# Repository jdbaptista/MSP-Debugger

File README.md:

## Introduction
This project is a combination of bare-metal firmware and hardware that displays the assembly instructions stored in the flash memory of an MSP430G2553, specifically the 20 pin DIP package. Please navigate to each section as necessary: [Example Operation](#example-operation), [Firmware](#firmware).

The device is shown below and supports the following button interactions:
* **UP**: Move back one instruction. Note that moving back one instruction is equivalent to moving lower in memory because the program counter increments positively each target CPU cycle.
  
* **DOWN**: Move forward one instruction. Note that moving forward one instruction is equivalent to moving higher in memory because the program counter increments positively each target CPU cycle.
  
* **FOLLOW JMP**: When the cursor is on a jump instruction, this button moves the cursor to the location specified by the jump. There is also support for following call instructions when the destination operand is an immediate or PC relative offset.
  
* **BIN <-> ASM**: Switch the display view between machine code (binary), displayed in hexadecimal, and RISC assembly instructions. This button highlights that assembly instructions on the target correspond to variable length machine code due to operand types.
  
* **RESET**: Move the cursor back to `0xC000`, which is the start of code memory. This is implemented by simply resetting the MCU.
  
* **USB RESET**: Reset the USB to UART bridge. USB data lines are currently in a broken state, so this button does nothing.

<br>

## Example Operation
The following example code from Texas Instruments is used in this example of the device's operation. The code blinks P1.0 repeatedly. Note that all assembly instructions displayed by the device are confirmed to be correct by Code Composer Studio's professional disassembler.
```C
#include <msp430.h>				

void main(void)
{
	WDTCTL = WDTPW | WDTHOLD;		// stop watchdog timer
	P1DIR |= 0x01;					// configure P1.0 as output

	volatile unsigned int i;		// volatile to prevent optimization

	while(1)
	{
		P1OUT ^= 0x01;				// toggle P1.0
		for(i=10000; i>0; i--);     // delay
	}
}
```
The target is loaded with the assembled machine code for this program and placed in the MSP-Debugger. Unfortunately, the display and USB to UART bridge are currently broken, so an MSP-FET (from any MSP430 development board) is connected to the JTAG header of the debugger. The MSP-FET's backchannel UART to USB bridge is used to convey instructions to the user, operating at **9600 baud with an 8-bit frame, no parity bit, and importantly 2 stop bits** (for data integrity). The UART encoding is ISO-8859-1, which is the default in CCS. Immediately after **RESET** the following instruction are extracted from the target and displayed.
```
0xC000: SUB.B #2 SP <
0xC002: MOV.B #0x5A80 &0x0120
0xC008: BIS.B #1 &0x0022
0xC00C: XOR.B #1 &0x0021
```
Using the **DOWN** button moves the cursor from `0xC000` to `0xC002`.
```
0xC002: MOV.B #0x5A80 &0x0120 <
0xC008: BIS.B #1 &0x0022
0xC00C: XOR.B #1 &0x0021
0xC010: MOV.B #0x2710 0x0000(SP)
```
An extremely well trained eye will recognize `&0x0120` as the location of the `WDTCTL` register, which can be confirmed by the peripheral file map on page 18 of the [MSP430G2x53 Datasheet](https://www.ti.com/lit/ds/symlink/msp430g2553.pdf?ts=1720602399535&ref_url=https%253A%252F%252Fwww.ti.com%252Fproduct%252FMSP430G2553%253Futm_source%253Dgoogle%2526utm_medium%253Dcpc%2526utm_campaign%253Depd-null-null-GPN_EN-cpc-pf-google-kr%2526utm_content%253DMSP430G2553%2526ds_k%253D%257B_dssearchterm%257D%2526DCM%253Dyes%2526gad_source%253D1%2526gclid%253DCjwKCAjw4ri0BhAvEiwA8oo6Fw8EdAuptheRVE8vx0Q2j3G3iyDjTU-aOLXieh8M-imSlC9cQUR6_hoClwEQAvD_BwE%2526gclsrc%253Daw.ds%2526bm-verify%253DAAQAAAAJ_____3QLXOZbbdruMI2eB4mFy5KSyEb-yU9yfcNR8-6ZE-F4IlQA15TnUbnZYGHUclM_YK0JJvwZfmZV1vz0BoNFahgPHVY7BCm4W1e8hj6dfjPbReoJt03aw_CYG9J3Y8_jl0rNTcSpbsnRtODv2ub_rMMIkYIZ8sZN9mj6PYFAQ1CDy5mA6PGPGiCbLLn4tzBTBUOk0bJGTj9kveVfehS7i0km-maJESLOX2xoAFatjT2Bv-a8B9gvZcxtGENvp6eMYJDLbmRf67x4X7TE7tt88LH3n9FraEEjZPNjqllkWuL5OOONuBvPF598xP5kkYnJk3wzH9hIroxr1CUU2mTA124pgKzPR_rSHUN9RBbZlIETbuTA60Tk97_1ntDEeGNxAcWS2jB9cD66YYZ0SP0K35RqUrqlAPRsbdokSfG5fS__GGfM8jKUantdnKKpmyNt6DdoRJ1r1NB9CKWKb-SPG5tTHcpbzj1IFa38Zdux2S1X93eAYTW28T1i1pfPwFwJtyAuMkVxw52pn_Y16Fv4n5pcFP_gVm7DHllf_3j6l4I_ipVjaMjKLlI1TF2-Ir8mL8IGx4NuPwbIxyWDxJgmZ_jNEwqQak_lFWplGfgBfkp1_twV8Zrt-tub-1XrNvhwLE4xQLYsvy4ZATQQBHijVjMIYRRXAuL75RCAAUYcWCXUhR5zKtjJhYKP3NkYnMghe8Nj_tdsmRdDuz-CPD87). Someone without access to the C source code can reference page 363 of the [MSP430G2xx User Guide](https://www.ti.com/lit/ug/slau144k/slau144k.pdf?ts=1720622345813&ref_url=https%253A%252F%252Fwww.ti.com%252Fproduct%252FMSP430F2274-EP%253Fbm-verify%253DAAQAAAAJ_____2GXDeU4IIaEds7sCQitbINeDMGTgqNh7F20H7LVJyrs5LsYNIkQrF5ycgp2Z0Yzd4j0V7synm_dgqfLwBr7S5VesPGUssLDDUfg7mGj_mgtHY82RE3zgMG80y9GDnAMYK8hv1U5Bq9QLLAvt0XehujFdDcILVLVdafgQQ4y_G74JWcE-jRRkwir5ItF99koK6Pg_AP0E-3rrXrP4YO819zT--lXgtbtaeA9YqF_kJtLNL18SaURyUQHTQi5XznOoq8sb0SznRHjyRujqGne18cY0YsrFImOVD6oPzmZqavXlbABc6vvCKw) to determine that the value `#0x5A80` being moved into `WDTCTL` register writes the correct watchdog password `0x5A00` (`WDTPW`) and suspends the watchdog's operation with `0x0080` (`WDTHOLD`). The watchdog timer will reset the microcontroller if not 'pet' in time by setting `WDTCNTCL`, so this instruction allows the microcontroller to operate without fear of the watchdog.

Using the **BIN <-> ASM** button switches the display from assembly to machine code.
```
0xC002: 0x40B2 0x5A80 0x0120 <
0xC008: 0xD3D2 0x0022 
0xC00C: 0xE3D2 0x0021 
0xC010: 0x40B1 0x2710 0x0000 
```
In this view it can be seen that the instruction to suspend the watchdog takes 3 words, ie. 48 bits, to encode. This is because the `MOV` instruction is a double operand instruction type and the opcode `0x40B2` specifies immediate mode for the first operand, which stores the immediate in the second word, and absolute mode for the second operand, which stores its address in the third word. These modes are internally specified by indirect autoincrement mode with the PC register and indexed mode with the SR register, respectively.

The while loop on line 1 should correspond to a jump instruction somewhere in memory, which we navigate forward to discover.
```
0xC01A: JEQ 0xC00C <
0xC01C: SUB.B #1 0x0000(SP)
0xC020: CMP.B #0 0x0000(SP)
0xC024: JEQ 0xC00C
```
The first jump instruction found is at `0xC01A`, jumping to `0xC00C`. This isn't useful in itself because we don't know what was being compared, which was an instruction that was skipped over.

Using the **UP** button moves the cursor backward by one instruction.
```
0xC016: CMP.B #0 0x0000(SP) <
0xC01A: JEQ 0xC00C
0xC01C: SUB.B #1 0x0000(SP)
0xC020: CMP.B #0 0x0000(SP)
```
This instruction is comparing 0 to some variable located at the stack pointer. This should be `i` from line 12 of the source code because it is the only variable on the stack. Therefore, the jump must correspond to finishing the delay.

Moving the cursor down to the `JEQ 0xC00C` isntruction and using the **FOLLOW JMP** instruction brings the cursor to `0xC00C`.
```
0xC00C: XOR.B #1 &0x0021 <
0xC010: MOV.B #0x2710 0x0000(SP)
0xC016: CMP.B #0 0x0000(SP)
0xC01A: JEQ 0xC00C
```
Finally, it is seen that this `XOR` instruction corresponds to toggling P1.0, as it is the first thing to occur within the while loop!

## Firmware
An MSP430G2553, aside from being the target type, is also used as the main microcontroller for the device. Firmware was developed using register level C programming in Code Composer Studio. Development followed information derived from the [MSP430G2xx User Guide](https://www.ti.com/lit/ug/slau144k/slau144k.pdf?ts=1720622345813&ref_url=https%253A%252F%252Fwww.ti.com%252Fproduct%252FMSP430F2274-EP%253Fbm-verify%253DAAQAAAAJ_____2GXDeU4IIaEds7sCQitbINeDMGTgqNh7F20H7LVJyrs5LsYNIkQrF5ycgp2Z0Yzd4j0V7synm_dgqfLwBr7S5VesPGUssLDDUfg7mGj_mgtHY82RE3zgMG80y9GDnAMYK8hv1U5Bq9QLLAvt0XehujFdDcILVLVdafgQQ4y_G74JWcE-jRRkwir5ItF99koK6Pg_AP0E-3rrXrP4YO819zT--lXgtbtaeA9YqF_kJtLNL18SaURyUQHTQi5XznOoq8sb0SznRHjyRujqGne18cY0YsrFImOVD6oPzmZqavXlbABc6vvCKw), the [MSP430G2x53 Datasheet](https://www.ti.com/lit/ds/symlink/msp430g2553.pdf?ts=1720602399535&ref_url=https%253A%252F%252Fwww.ti.com%252Fproduct%252FMSP430G2553%253Futm_source%253Dgoogle%2526utm_medium%253Dcpc%2526utm_campaign%253Depd-null-null-GPN_EN-cpc-pf-google-kr%2526utm_content%253DMSP430G2553%2526ds_k%253D%257B_dssearchterm%257D%2526DCM%253Dyes%2526gad_source%253D1%2526gclid%253DCjwKCAjw4ri0BhAvEiwA8oo6Fw8EdAuptheRVE8vx0Q2j3G3iyDjTU-aOLXieh8M-imSlC9cQUR6_hoClwEQAvD_BwE%2526gclsrc%253Daw.ds%2526bm-verify%253DAAQAAAAJ_____3QLXOZbbdruMI2eB4mFy5KSyEb-yU9yfcNR8-6ZE-F4IlQA15TnUbnZYGHUclM_YK0JJvwZfmZV1vz0BoNFahgPHVY7BCm4W1e8hj6dfjPbReoJt03aw_CYG9J3Y8_jl0rNTcSpbsnRtODv2ub_rMMIkYIZ8sZN9mj6PYFAQ1CDy5mA6PGPGiCbLLn4tzBTBUOk0bJGTj9kveVfehS7i0km-maJESLOX2xoAFatjT2Bv-a8B9gvZcxtGENvp6eMYJDLbmRf67x4X7TE7tt88LH3n9FraEEjZPNjqllkWuL5OOONuBvPF598xP5kkYnJk3wzH9hIroxr1CUU2mTA124pgKzPR_rSHUN9RBbZlIETbuTA60Tk97_1ntDEeGNxAcWS2jB9cD66YYZ0SP0K35RqUrqlAPRsbdokSfG5fS__GGfM8jKUantdnKKpmyNt6DdoRJ1r1NB9CKWKb-SPG5tTHcpbzj1IFa38Zdux2S1X93eAYTW28T1i1pfPwFwJtyAuMkVxw52pn_Y16Fv4n5pcFP_gVm7DHllf_3j6l4I_ipVjaMjKLlI1TF2-Ir8mL8IGx4NuPwbIxyWDxJgmZ_jNEwqQak_lFWplGfgBfkp1_twV8Zrt-tub-1XrNvhwLE4xQLYsvy4ZATQQBHijVjMIYRRXAuL75RCAAUYcWCXUhR5zKtjJhYKP3NkYnMghe8Nj_tdsmRdDuz-CPD87), and the [MSP430 JTAG Programming Guide](https://www.ti.com/lit/ug/slau320aj/slau320aj.pdf?ts=1720599451382&ref_url=https%253A%252F%252Fwww.google.com%252F). Three libraries were developed to handle separate facets of the project requirements:

* **UART Driver**: This library handles control of the USCI peripheral to communicate via the UART module. This driver handles configuration of USCI and UART registers, buffering of user printing output, and transmission with a builtin interrupt handler. The driver offers a user-friendly API (ex. `wait_print(char *input)` and `uart_print_hex(uint16_t input)`) optimized for spaced calls. The `wait_print` function is most likely to be used, and currently implements polling until the previous message is finished being sent.
  
* **JTAG Driver**: This library handles interfacing with the target through its JTAG debugging interface. Internally, the interface is implemented as an FSM that is controlled by five input and output lines: TDI, TDO, TMS, TCK, and TEST. This driver works by bit banging the correct FSM sequences on GPIO pins. The API offers a variety of functions (specified by the [JTAG Programming Guide](https://www.ti.com/lit/ug/slau320aj/slau320aj.pdf?ts=1720599451382&ref_url=https%253A%252F%252Fwww.google.com%252F)), but the most important for this project is `readMem(uint16_t address)`. This function returns the value stored in the target at a particular memory address.
  
* **Disassembler**: This library handles conversion of machine code to RISC assembly instruction. Information about the representation of each instruction as machine code can be found in the [MSP430G2xx User Guide](https://www.ti.com/lit/ug/slau144k/slau144k.pdf?ts=1720622345813&ref_url=https%253A%252F%252Fwww.ti.com%252Fproduct%252FMSP430F2274-EP%253Fbm-verify%253DAAQAAAAJ_____2GXDeU4IIaEds7sCQitbINeDMGTgqNh7F20H7LVJyrs5LsYNIkQrF5ycgp2Z0Yzd4j0V7synm_dgqfLwBr7S5VesPGUssLDDUfg7mGj_mgtHY82RE3zgMG80y9GDnAMYK8hv1U5Bq9QLLAvt0XehujFdDcILVLVdafgQQ4y_G74JWcE-jRRkwir5ItF99koK6Pg_AP0E-3rrXrP4YO819zT--lXgtbtaeA9YqF_kJtLNL18SaURyUQHTQi5XznOoq8sb0SznRHjyRujqGne18cY0YsrFImOVD6oPzmZqavXlbABc6vvCKw), specifically the CPU section. The MSP430G2553 contains a 16-bit CPU supporting variable length instructions ranging from a minimum of 1 word to a maximum of 3 words. This presented a significant design challenge as moving one assembly instruction backward is ambiguously a shift of 1, 2, or 3 words in memory with little to hint at which is correct. This ambiguity stems from the various addressing modes (ex. indexed mode) and instruction types (ex. single operand). The disassembler has no remedy to this issue; rather, it is currently solved by the main program which simply begins from the beginning of flash memory and iterates forward until finding the correct instruction. It is planned to speed up this process with a significantly sized cache of nearby instruction locations.

The main program handles user button input with interrupts on the corresponding GPIO pins and a simple button debounce system using the timer peripheral. The program enters LPM3 while waiting for user input, with the timer running on ACLK sourced from the 12kHz VLO waking the program up if a button debounce has finished.

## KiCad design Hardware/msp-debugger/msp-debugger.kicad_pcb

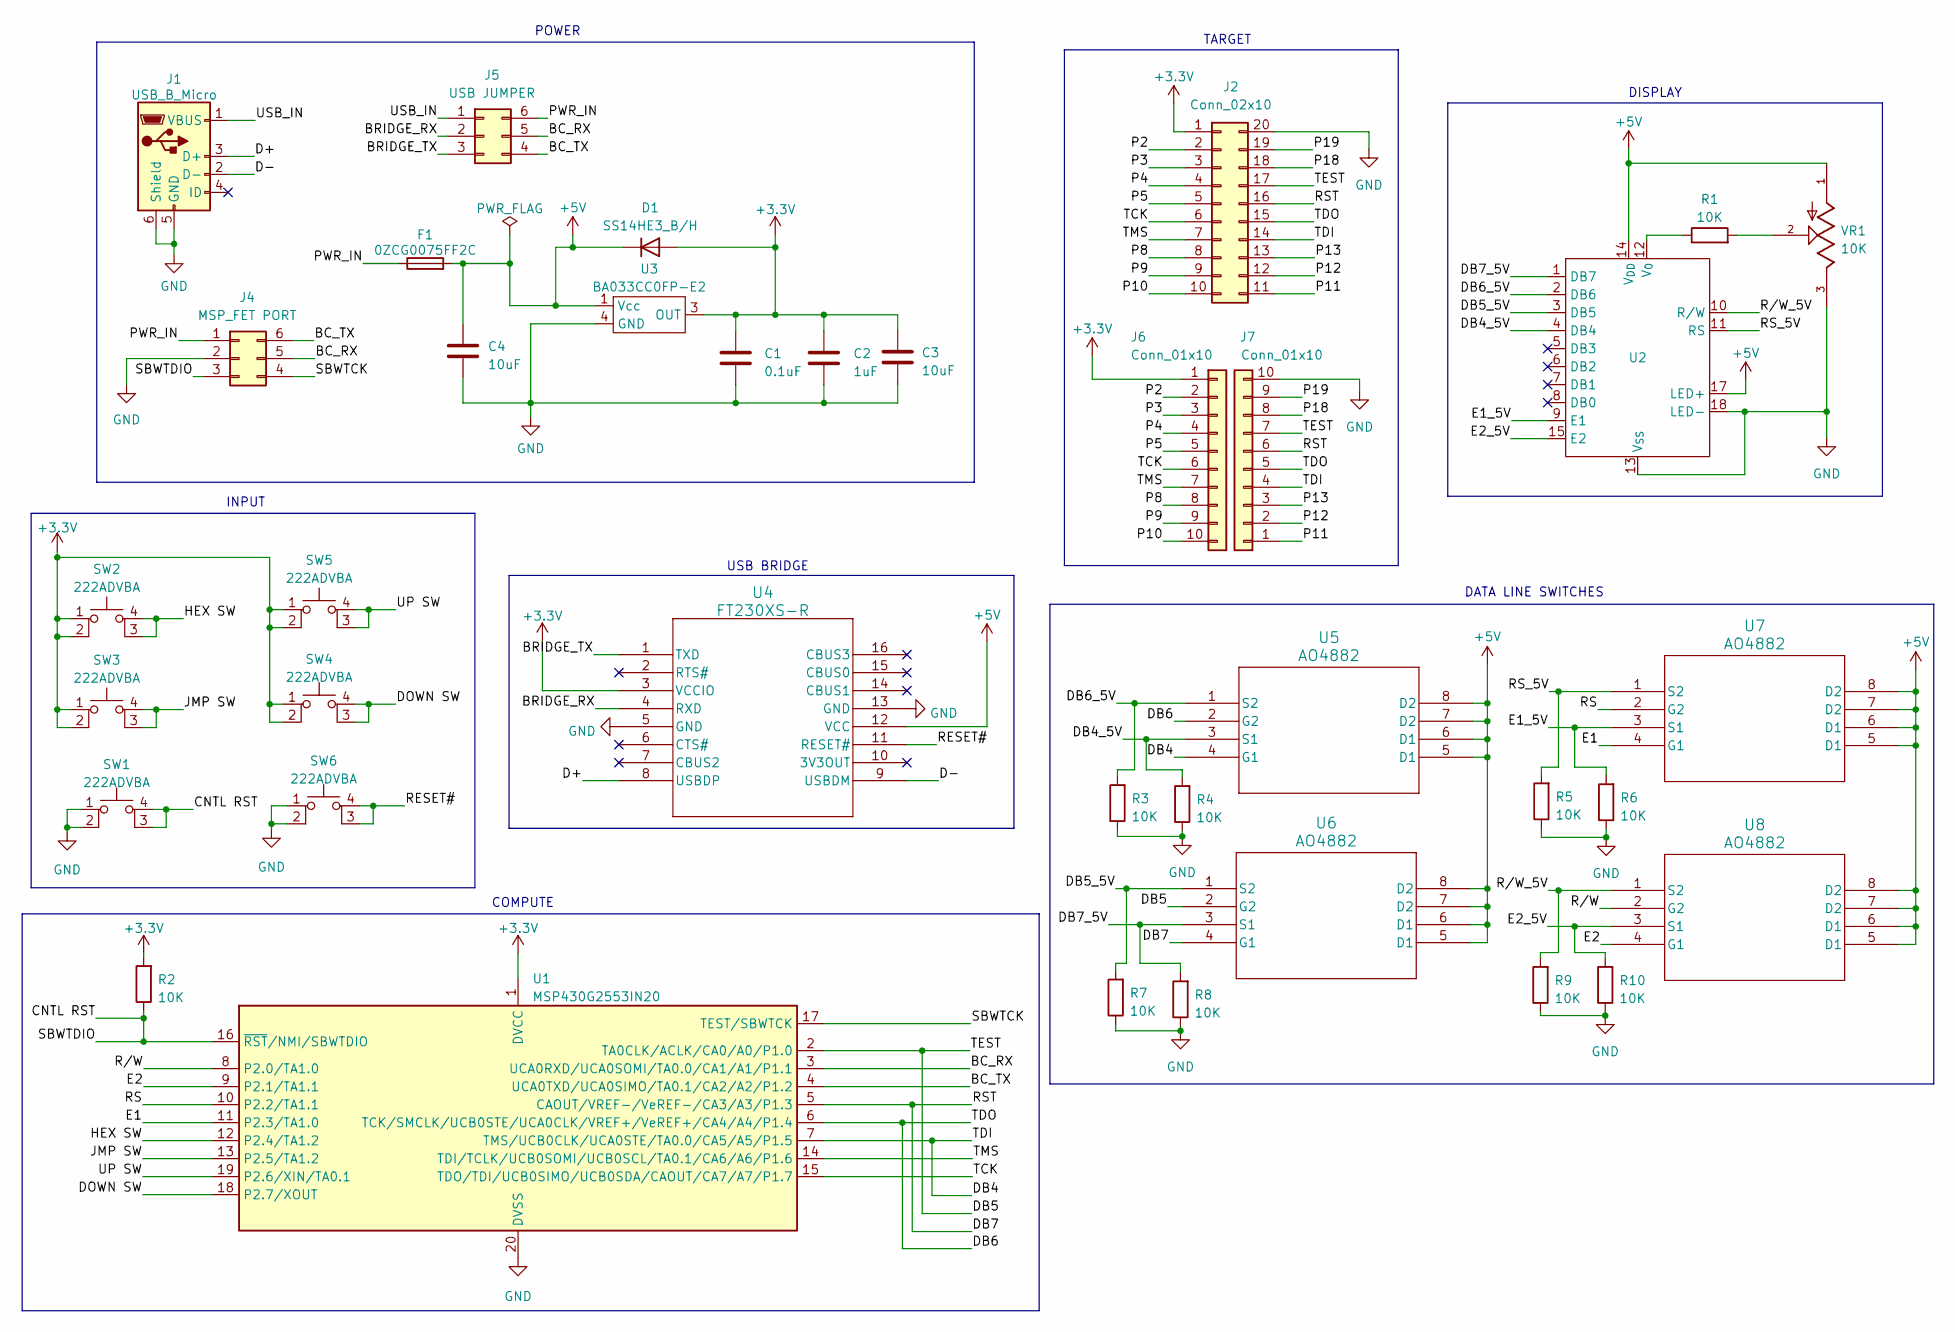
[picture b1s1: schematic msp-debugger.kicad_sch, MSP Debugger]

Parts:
C1: 0.1uF; C_0805_2012Metric
C2: 1uF; C_0805_2012Metric
C3, C4: 10uF; C_0805_2012Metric
D1: SS14HE3_B/H; D_SMA
F1: 0ZCG0075FF2C; Fuse_1812_4532Metric
J1: USB_B_Micro; PinHeader_1x05_P2.54mm_Vertical
J2: Conn_02x10; DIL_CONN_110-83-320-41-001101
J4: MSP_FET PORT; PinHeader_2x03_P2.54mm_Vertical
J5: USB JUMPER; PinHeader_2x03_P2.54mm_Vertical
J6, J7: Conn_01x10; PinHeader_1x10_P2.54mm_Vertical
R1, R2, R3, R4, R5, R6, R7, R8, R9, R10: 10K; C_0805_2012Metric
SW1, SW2, SW3, SW4, SW5, SW6: 222ADVBA; SW_222ADVBA
U1: MSP430G2553IN20; DIP-20_W7.62mm
U2: PinHeader_2x09_P2.54mm_Vertical
U3: BA033CC0FP-E2; TO-252-3
U4: FT230XS-R; SOIC_30XS-R_FTD
U5, U6, U7, U8: AO4882; SO-8_AOS
VR1: 10K; TRIM_3362P-1-103LF; PARTREV 08/26/10

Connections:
+3.3V: C1.2, C2.1, C3.1, D1.2 (A), J2.1, J6.1, R2.2, SW2.1, SW2.2, SW3.1, SW3.2, SW4.1, SW4.2, SW5.1, SW5.2, U1.1 (DVCC), U3.3 (OUT), U4.3 (VCCIO)
+5V: C4.1, D1.1 (K), F1.2, U2.14 (V_{DD}), U2.17 (LED+), U3.1 (Vcc), U4.12 (VCC), U5.5 (D1), U5.6 (D1), U5.7 (D2), U5.8 (D2), U6.5 (D1), U6.6 (D1), U6.7 (D2), U6.8 (D2), U7.5 (D1), U7.6 (D1), U7.7 (D2), U7.8 (D2), U8.5 (D1), U8.6 (D1), U8.7 (D2), U8.8 (D2), VR1.1
/BC_RX: J4.5, J5.5, U1.3 (UCA0RXD/UCA0SOMI/TA0.0/CA1/A1/P1.1)
/BC_TX: J4.6, J5.4, U1.4 (UCA0TXD/UCA0SIMO/TA0.1/CA2/A2/P1.2)
/BRIDGE_RX: J5.2, U4.4 (RXD)
/BRIDGE_TX: J5.3, U4.1 (TXD)
/CNTL RST: J4.3, R2.1, SW1.3 (K), SW1.4 (A), U1.16 (~RST/NMI/SBWTDIO)
/D+: J1.3 (D+), U4.8 (USBDP)
/D-: J1.2 (D-), U4.9 (USBDM)
/DB4: J2.14, J7.4, U1.7 (TMS/UCB0CLK/UCA0STE/TA0.0/CA5/A5/P1.5), U5.4 (G1)
/DB4_5V: R4.2, U2.4 (DB4), U5.3 (S1)
/DB5: J2.17, J7.7, U1.2 (TA0CLK/ACLK/CA0/A0/P1.0), U6.2 (G2)
/DB5_5V: R7.2, U2.3 (DB5), U6.1 (S2)
/DB6: J2.15, J7.5, U1.6 (TCK/SMCLK/UCB0STE/UCA0CLK/VREF+/VeREF+/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), U5.2 (G2)
/DB6_5V: R3.2, U2.2 (DB6), U5.1 (S2)
/DB7: J2.16, J7.6, U1.5 (CAOUT/VREF-/VeREF-/CA3/A3/P1.3), U6.4 (G1)
/DB7_5V: R8.2, U2.1 (DB7), U6.3 (S1)
/DOWN SW: SW4.3 (K), SW4.4 (A), U1.18 (P2.7/XOUT)
/E1: U1.11 (P2.3/TA1.0), U7.4 (G1)
/E1_5V: R6.2, U2.9 (E1), U7.3 (S1)
/E2: U1.9 (P2.1/TA1.1), U8.4 (G1)
/E2_5V: R10.2, U2.15 (E2), U8.3 (S1)
/HEX SW: SW2.3 (K), SW2.4 (A), U1.12 (P2.4/TA1.2)
/JMP SW: SW3.3 (K), SW3.4 (A), U1.13 (P2.5/TA1.2)
/P2: J2.2, J6.2
/P3: J2.3, J6.3
/P4: J2.4, J6.4
/P5: J2.5, J6.5
/P8: J2.8, J6.8
/P9: J2.9, J6.9
/P10: J2.10, J6.10
/P11: J2.11, J7.1
/P12: J2.12, J7.2
/P13: J2.13, J7.3
/P18: J2.18, J7.8
/P19: J2.19, J7.9
/PWR_IN: F1.1, J4.1, J5.6
/RESET#: SW6.3 (K), SW6.4 (A), U4.11 (RESET#)
/RS: U1.10 (P2.2/TA1.1), U7.2 (G2)
/RS_5V: R5.2, U2.11 (RS), U7.1 (S2)
/R/W: U1.8 (P2.0/TA1.0), U8.2 (G2)
/R/W_5V: R9.2, U2.10 (R/W), U8.1 (S2)
/SBWTCK: J4.4, U1.17 (TEST/SBWTCK)
/TCK: J2.6, J6.6, U1.15 (TDO/TDI/UCB0SIMO/UCB0SDA/CAOUT/CA7/A7/P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)
/TMS: J2.7, J6.7, U1.14 (TDI/TCLK/UCB0SOMI/UCB0SCL/TA0.1/CA6/A6/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)
/UP SW: SW5.3 (K), SW5.4 (A), U1.19 (P2.6/XIN/TA0.1)
/USB_IN: J1.1 (VBUS), J5.1
GND: C1.1, C2.2, C3.2, C4.2, J1.5 (GND), J1.6 (Shield), J2.20, J4.2, J7.10, R3.1, R4.1, R5.1, R6.1, R7.1, R8.1, R9.1, R10.1, SW1.1, SW1.2, SW6.1, SW6.2, U1.20 (DVSS), U2.13 (V_{SS}), U2.18 (LED-), U3.4 (GND), U4.5 (GND), U4.13 (GND), VR1.3
unnamed: R1.2, VR1.2
unnamed: R1.1, U2.12 (V_{0})

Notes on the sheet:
POWER
DATA LINE SWITCHES
USB BRIDGE
INPUT
COMPUTE
TARGET
DISPLAY

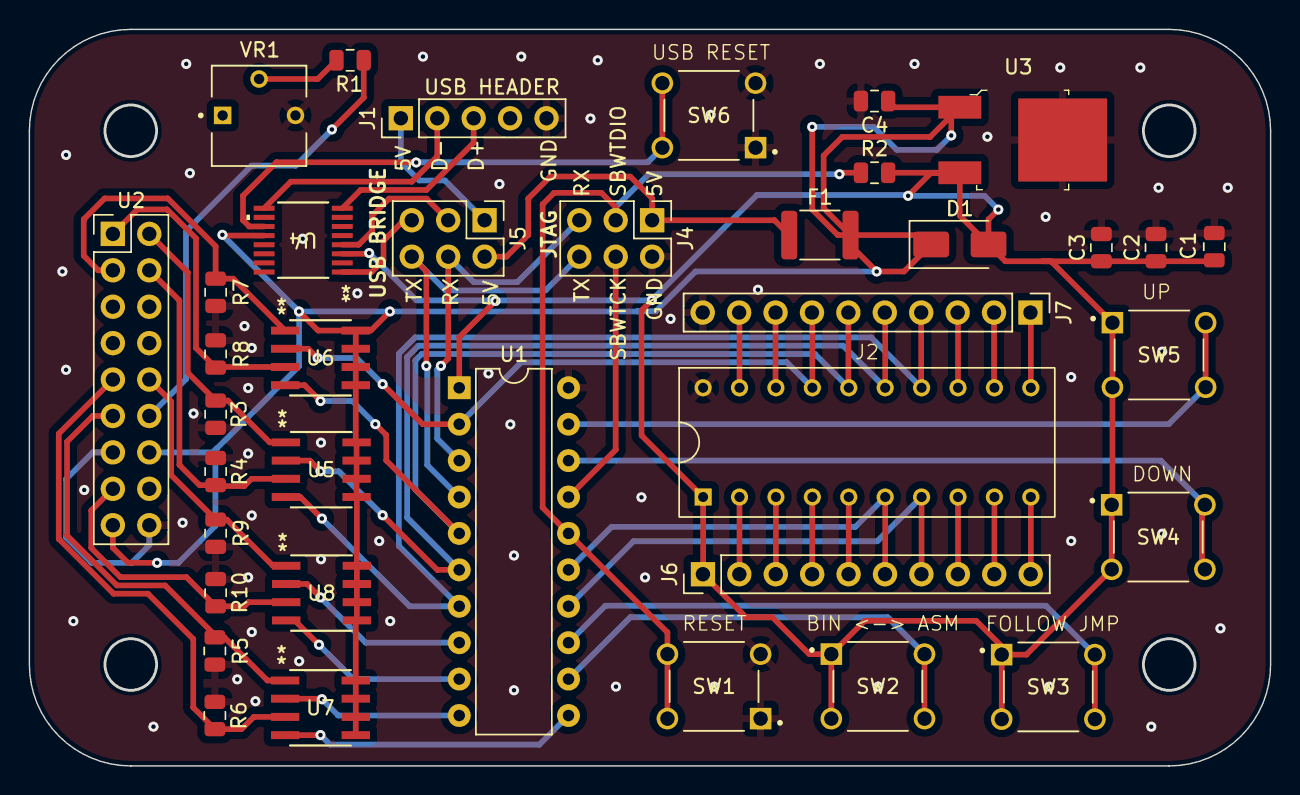
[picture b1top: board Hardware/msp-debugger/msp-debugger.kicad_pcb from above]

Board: 2 copper layers, 86.5 x 51.3 mm, 37 parts (0 on the bottom side), 50 nets.

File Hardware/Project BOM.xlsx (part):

Partner 1 Name: Jaden Baptista | Partner 1 Email: baptistajaden@berkeley.edu | Partner 2 Name: Anthony Rubio | Partner 2 Email: anthonyjrubio@berkeley.edu
 |  |  |  |  |  |  |  |  |  | Total Price for Project
 |  |  |  |  |  |  |  |  |  | 59.543329999999997
Qty (for 1 board) | Manufacturer Part # | Digi-key Part#/SKU | Price/unit ($) | Purchase URL | Reference Designator | Description (include component value if applicable) | Datasheet Link | Multiple | Total Qty | Total Price/part ($)
1 | NHD-0440AZ-FL-YBW | NHD-0440AZ-FL-YBW-ND | 28.59 | https://www.digikey.com/en/products/detail/newhaven-display-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 | U2 | LCD MOD 160 DIG 40X4 TRANS YLW/GRN | https://newhavendisplay.com/content/specs/NHD-0440AZ-FL-YBW.pdf | 1 | 1 | 28.59
10 | RC0805JR-0710KL | 311-10KARCT-ND | 0.1 | https://www.digikey.com/en/products/detail/yageo/RC0805JR-07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 | R1 | RES 10K OHM 5% 1/8W 0805 | https://www.yageo.com/upload/media/product/productsearch/dat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 | 1 | 10 | 1
1 | 3362P-1-103LF | 3362P-103LF-ND | 1.03 | https://www.digikey.com/en/products/detail/bourns-inc/3362P-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 | VR1 | TRIMMER 10K OHM 0.5W PC PIN TOP | https://www.bourns.com/docs/Product-Datasheets/3362.pdf | 1 | 1 | 1.03
6 | 222ADVBA | CT3084-ND | 0.23 | https://www.digikey.com/en/products/detail/cts-electrocompon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 | SW(1-5) | SWITCH TACTILE SPST-NO 0.05A 12V | https://www.ctscorp.com/wp-content/uploads/222A.pdf | 1 | 6 | 1.3800000000000001
3 | CL21B104KBCNNNC | 1276-1003-1-ND | 0.1 | https://www.digikey.com/en/products/detail/samsung-electro-m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 | C2, C5, C6 | CAP CER 0.1UF 50V X7R 0805 | https://media.digikey.com/pdf/Data%20Sheets/Samsung%20PDFs/C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 | 1 | 3 | 0.30000000000000004
2 | MSP430G2553IN20 | 296-28429-5-ND | 2.9 | https://www.digikey.com/en/products/detail/texas-instruments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 | U1, J1 | IC MCU 16BIT 16KB FLASH 20DIP | https://www.ti.com/general/docs/suppproductinfo.tsp?distId=1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 | 1 | 2 | 5.8
1 | 110-83-320-41-001101 | 110-83-320-41-001101-ND | 2.02 | https://www.digikey.com/en/products/detail/preci-dip/110-83-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 | J2 | CONN IC DIP SOCKET 20POS GOLD | https://www.mouser.com/datasheet/2/571/Preci_Dip_01252017_ca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 | 1 | 1 | 2.02
1 | CL21B105KAFNNNE | 1276-1066-1-ND | 0.1 | https://www.digikey.com/en/products/detail/samsung-electro-m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 | C1 | 1 µF ±10% 25V Ceramic Capacitor X7R 0805 (2012 Metric) | https://media.digikey.com/pdf/Data%20Sheets/Samsung%20PDFs/C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 | 1 | 1 | 0.1
1 | BA033CC0FP-E2 | BA033CC0FP-E2CT-ND | 1.41 | https://www.digikey.com/en/products/detail/rohm-semiconducto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 | U3 | IC REG LINEAR 3.3V 1A TO252-3 | https://www.rohm.com/datasheet?p=BA033CC0FP&dist=Digi-key&me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 | 1 | 1 | 1.41
1 | SS14HE3_B/H | 112-SS14HE3_B/HCT-ND | 9.7519999999999996E-2 | https://www.digikey.com/en/products/detail/vishay-general-se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 | D1 | Diode 40 V 1A Surface Mount DO-214AC (SMA) | https://www.vishay.com/docs/88746/ss12.pdf | 1 | 1 | 9.7519999999999996E-2
1 | 10118194-0011LF | 10118194-0011LF-ND | 0.27581 | https://www.digikey.com/en/products/detail/amphenol-icc-fci/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 | J1 | USB - micro B USB 2.0 Receptacle Connector 5 Position Surface Mount, Right Angl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 | https://cdn.amphenol-cs.com/media/wysiwyg/files/drawing/1011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 | 1 | 1 | 0.27581
1 | 0ZCG0075FF2C | 507-1763-1-ND | 0.16 | https://www.digikey.com/en/products/detail/bel-fuse-inc/0ZCG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 | F1 | PTC RESET FUSE 16V 750MA 1812 | https://www.belfuse.com/resources/datasheets/circuitprotecti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 | 1 | 1 | 0.16
2 | CL21A106KOQNNNE | 1276-1096-1-ND | 0.1 | https://www.digikey.com/en/products/detail/samsung-electro-m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 | C3, C4 | 10 µF ±10% 16V Ceramic Capacitor X5R 0805 (2012 Metric) | https://media.digikey.com/pdf/Data%20Sheets/Samsung%20PDFs/C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 | 1 | 2 | 0.2
1 | FT230XS-R | 768-1135-1-ND | 2.2599999999999998 | https://www.digikey.com/en/products/detail/ftdi-future-techn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 | U4 | IC USB SERIAL BASIC UART 16SSOP | https://ftdichip.com/wp-content/uploads/2021/10/DS_FT230X.pdf | 1 | 1 | 2.2599999999999998
4 | AO4882 | 785-1317-1-ND | 0.52 | https://www.digikey.com/en/products/detail/alpha-omega-semic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 |  | Mosfet Array 40V 8A 2W Surface Mount 8-SOIC | https://www.digikey.com/htmldatasheets/production/1034359/0/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 | 1 | 4 | 2.08
2 | TSW-102-07-G-T | TSW-102-07-G-T-ND | 0.73 | https://www.digikey.com/en/products/detail/samtec-inc/TSW-10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 | J4, J5 | CONN HEADER VERT 6POS 2.54MM | https://mm.digikey.com/Volume0/opasdata/d220001/medias/docus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 | 1 | 2 | 1.46
3 | QPC02SXGN-RC | S9337-ND | 0.1 | https://www.digikey.com/en/products/detail/sullins-connector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 |  | CONN JUMPER SHORTING .100" GOLD | https://s3.amazonaws.com/catalogspreads-pdf/PAGE128-129%20.1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 | 1 | 3 | 0.30000000000000004
2 | TD-109-T-A | SAM1114-09-ND | 3.6 | https://www.digikey.com/en/products/detail/samtec-inc/TD-109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 |  | CONN HEADER VERT 18POS 2.54MM | https://suddendocs.samtec.com/catalog_english/td.pdf | 1 | 2 | 7.2
2 | TS-110-T-A | SAM1112-10-ND | 1.94 | https://www.digikey.com/en/products/detail/samtec-inc/TS-110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 |  | CONN HEADER VERT 10POS 2.54MM | https://suddendocs.samtec.com/catalog_english/td.pdf | 1 | 2 | 3.88
 |  |  |  |  |  |  |  |  | 0 | 0
 |  |  |  |  |  |  |  |  | 0 | 0
 |  |  |  |  |  |  |  |  | 0 | 0
 |  |  |  |  |  |  |  |  | 0 | 0
 |  |  |  |  |  |  |  |  | 0 | 0
 |  |  |  |  |  |  |  |  | 0 | 0
 |  |  |  |  |  |  |  |  | 0 | 0
 |  |  |  |  |  |  |  |  | 0 | 0
 |  |  |  |  |  |  |  |  | 0 | 0
 |  |  |  |  |  |  |  |  | 0 | 0
 |  |  |  |  |  |  |  |  | 0 | 0
 |  |  |  |  |  |  |  |  | 0 | 0
 |  |  |  |  |  |  |  |  | 0 | 0
 |  |  |  |  |  |  |  |  | 0 | 0
 |  |  |  |  |  |  |  |  | 0 | 0
 |  |  |  |  |  |  |  |  | 0 | 0
 |  |  |  |  |  |  |  |  | 0 | 0
 |  |  |  |  |  |  |  |  | 0 | 0
 |  |  |  |  |  |  |  |  | 0 | 0
 |  |  |  |  |  |  |  |  | 0 | 0
 |  |  |  |  |  |  |  |  | 0 | 0
 |  |  |  |  |  |  |  |  | 0 | 0
 |  |  |  |  |  |  |  |  | 0 | 0
 |  |  |  |  |  |  |  |  | 0 | 0
 |  |  |  |  |  |  |  |  | 0 | 0
 |  |  |  |  |  |  |  |  | 0 | 0
 |  |  |  |  |  |  |  |  | 0 | 0
 |  |  |  |  |  |  |  |  | 0 | 0
 |  |  |  |  |  |  |  |  | 0 | 0
 |  |  |  |  |  |  |  |  | 0 | 0
 |  |  |  |  |  |  |  |  | 0 | 0
 |  |  |  |  |  |  |  |  | 0 | 0
 |  |  |  |  |  |  |  |  | 0 | 0
 |  |  |  |  |  |  |  |  | 0 | 0
 |  |  |  |  |  |  |  |  | 0 | 0
 |  |  |  |  |  |  |  |  | 0 | 0
 |  |  |  |  |  |  |  |  | 0 | 0
 |  |  |  |  |  |  |  |  | 0 | 0
 |  |  |  |  |  |  |  |  | 0 | 0
 |  |  |  |  |  |  |  |  | 0 | 0
 |  |  |  |  |  |  |  |  | 0 | 0
 |  |  |  |  |  |  |  |  | 0 | 0
 |  |  |  |  |  |  |  |  | 0 | 0
 |  |  |  |  |  |  |  |  | 0 | 0
 |  |  |  |  |  |  |  |  | 0 | 0
 |  |  |  |  |  |  |  |  | 0 | 0
 |  |  |  |  |  |  |  |  | 0 | 0
 |  |  |  |  |  |  |  |  | 0 | 0
 |  |  |  |  |  |  |  |  | 0 | 0
 |  |  |  |  |  |  |  |  | 0 | 0
 |  |  |  |  |  |  |  |  | 0 | 0
 |  |  |  |  |  |  |  |  | 0 | 0
 |  |  |  |  |  |  |  |  | 0 | 0
 |  |  |  |  |  |  |  |  | 0 | 0
 |  |  |  |  |  |  |  |  | 0 | 0
 |  |  |  |  |  |  |  |  | 0 | 0
 |  |  |  |  |  |  |  |  | 0 | 0
 |  |  |  |  |  |  |  |  | 0 | 0
 |  |  |  |  |  |  |  |  | 0 | 0
 |  |  |  |  |  |  |  |  | 0 | 0
 |  |  |  |  |  |  |  |  | 0 | 0
 |  |  |  |  |  |  |  |  | 0 | 0
 |  |  |  |  |  |  |  |  | 0 | 0
 |  |  |  |  |  |  |  |  | 0 | 0
 |  |  |  |  |  |  |  |  | 0 | 0
 |  |  |  |  |  |  |  |  | 0 | 0
 |  |  |  |  |  |  |  |  | 0 | 0
 |  |  |  |  |  |  |  |  | 0 | 0
 |  |  |  |  |  |  |  |  | 0 | 0
 |  |  |  |  |  |  |  |  | 0 | 0
 |  |  |  |  |  |  |  |  | 0 | 0
 |  |  |  |  |  |  |  |  | 0 | 0
 |  |  |  |  |  |  |  |  | 0 | 0
 |  |  |  |  |  |  |  |  | 0 | 0
 |  |  |  |  |  |  |  |  | 0 | 0
 |  |  |  |  |  |  |  |  | 0 | 0
 |  |  |  |  |  |  |  |  | 0 | 0
 |  |  |  |  |  |  |  |  | 0 | 0
 |  |  |  |  |  |  |  |  | 0 | 0
 |  |  |  |  |  |  |  |  | 0 | 0
 |  |  |  |  |  |  |  |  | 0 | 0
 |  |  |  |  |  |  |  |  | 0 | 0
 |  |  |  |  |  |  |  |  | 0 | 0
 |  |  |  |  |  |  |  |  | 0 | 0
 |  |  |  |  |  |  |  |  | 0 | 0
 |  |  |  |  |  |  |  |  | 0 | 0
 |  |  |  |  |  |  |  |  | 0 | 0
 |  |  |  |  |  |  |  |  | 0 | 0
 |  |  |  |  |  |  |  |  | 0 | 0
 |  |  |  |  |  |  |  |  | 0 | 0
 |  |  |  |  |  |  |  |  | 0 | 0
 |  |  |  |  |  |  |  |  | 0 | 0
 |  |  |  |  |  |  |  |  | 0 | 0
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
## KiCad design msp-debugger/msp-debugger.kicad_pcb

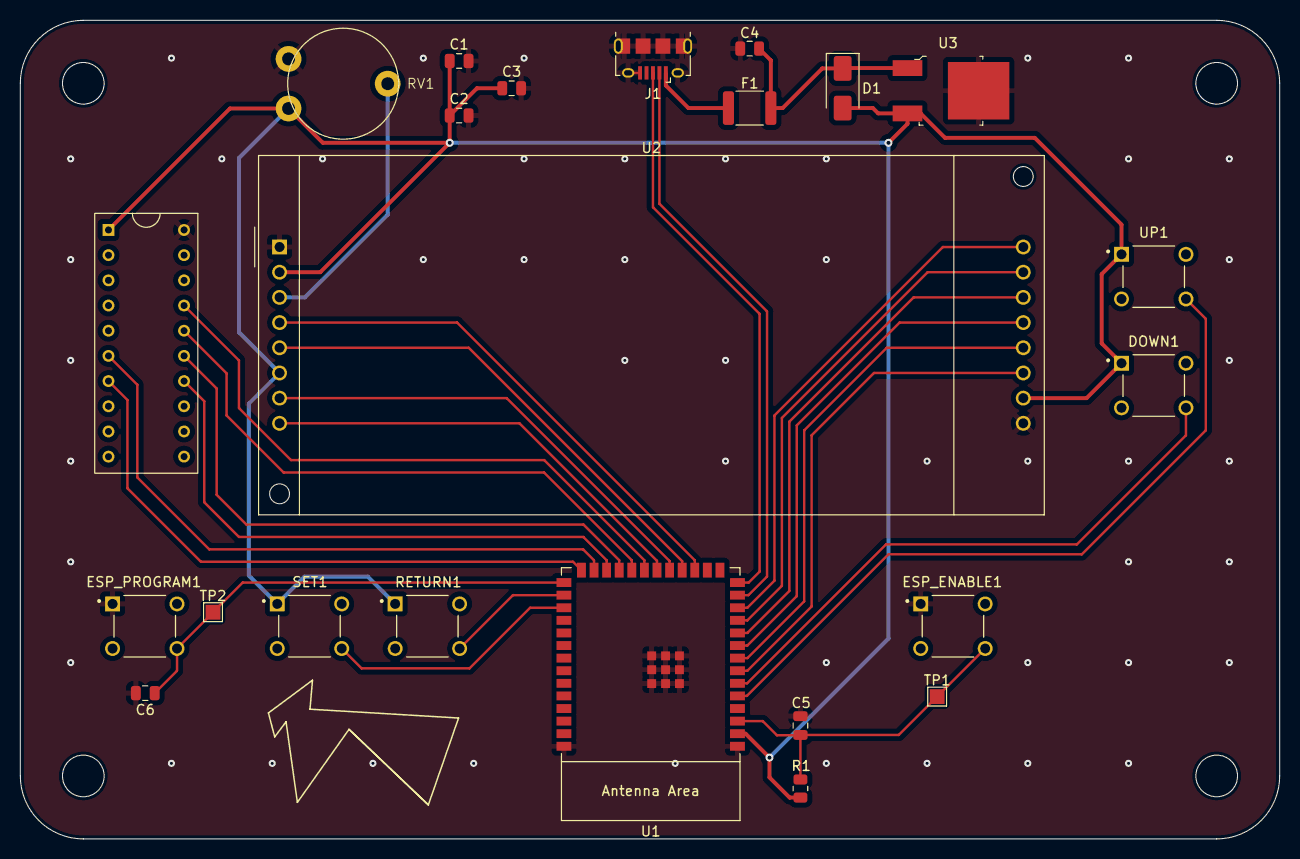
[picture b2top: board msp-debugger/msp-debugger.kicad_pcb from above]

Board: 2 copper layers, 127.0 x 82.5 mm, 23 parts (0 on the bottom side), 29 nets.

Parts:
C1: 1uF; C_0805_2012Metric
C2, C5, C6: 0.1uF; C_0805_2012Metric
C3, C4: 10uF; C_0805_2012Metric
D1: SS14HE3_B/H; D_SMA
DOWN1: 222ADVBA; SW_222ADVBA
ESP_ENABLE1: 222ADVBA; SW_222ADVBA
ESP_PROGRAM1: 222ADVBA; SW_222ADVBA
F1: 0ZCG0075FF2C; Fuse_1812_4532Metric
J1: USB_B_Micro; USB_Micro-B_Amphenol_10118194_Horizontal
J2: Conn_02x10; DIL_CONN_110-83-320-41-001101
R1: 10k; R_0805_2012Metric
RETURN1: 222ADVBA; SW_222ADVBA
RV1: 10K-20K; Potentiometer_CTS_PTN10-E20HB20
SET1: 222ADVBA; SW_222ADVBA
TP1, TP2: TestPoint; TestPoint_Pad_1.5x1.5mm
U1: ESP32-S2-SOLO
U2: NHD-0420H1Z
U3: BA033CC0FP-E2; TO-252-3
UP1: 222ADVBA; SW_222ADVBA

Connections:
+3.3V: C1.1, C2.1, C3.1, D1.2 (A), DOWN1.1, J2.1, R1.1, RETURN1.1, RV1.3, SET1.1, U1.2 (3V3), U2.2 (VDD), U2.6 (E), U2.15 (A), U3.3 (OUT), UP1.1
/D+: J1.3 (D+), U1.14 (GPIO20/U1CTS/ADC2_CH9/CLK_OUT1/USB_D+)
/D-: J1.2 (D-), U1.13 (GPIO19/U1RTS/ADC2_CH8/CLK_OUT2/USB_D-)
/DB0: U1.19 (GPIO11/TOUCH11/ADC2_CH0/FSPID/FSPIIO5), U2.7 (DB0)
/DB1: U1.20 (GPIO12/TOUCH12/ADC2_CH1/FSPICLK/FSPIIO6), U2.8 (DB1)
/DB2: U1.12 (GPIO8/TOUCH8/ADC1_CH7), U2.9 (DB2)
/DB3: U1.11 (GPIO18/U1RXD/ADC2_CH7/DAC_2/CLK_OUT3), U2.10 (DB3)
/DB4: U1.10 (GPIO17/U1TXD/ADC2_CH6/DAC_1), U2.11 (DB4)
/DB5: U1.9 (GPIO16/U0CTS/ADC2_CH5/XTAL_32K_N), U2.12 (DB5)
/DB6: U1.8 (GPIO15/U0RTS/ADC2_CH4/XTAL_32K_P), U2.13 (DB6)
/DB7: U1.7 (GPIO7/TOUCH7/ADC1_CH6), U2.14 (DB7)
/DOWN SW: DOWN1.4 (A), U1.6 (GPIO6/TOUCH6/ADC1_CH5)
/ESP EN: C5.1, ESP_ENABLE1.4 (A), R1.2, TP1.1, U1.3 (EN)
/ESP PROG SW: C6.1, ESP_PROGRAM1.4 (A), TP2.1, U1.27 (GPIO0)
/LCD RS: U1.17 (GPIO9/TOUCH9/ADC1_CH8/FSPIHD), U2.4 (RS)
/LCD R/W: U1.18 (GPIO10/TOUCH10/ADC1_CH9/FSPICS0/FSPIIO4), U2.5 (R/W)
/RET SW: RETURN1.4 (A), U1.28 (SPIIO6/GPIO35/FSPID)
/RST: J2.16, U1.22 (GPIO14/TOUCH14/ADC2_CH3/FSPIWP/FSPIDQS)
/SET SW: SET1.4 (A), U1.29 (SPIIO7/GPIO36/FSPICLK)
/TCK: J2.6, U1.25 (SPIIO5/GPIO34/FSPICS0)
/TDI: J2.14, U1.24 (SPIIO4/GPIO33/FSPIHD)
/TDO: J2.15, U1.23 (GPIO21)
/TEST: J2.17, U1.21 (GPIO13/TOUCH13/ADC2_CH2/FSPIQ/FSPIIO7)
/TMS: J2.7, U1.26 (GPIO45)
/UP SW: U1.5 (GPIO5/TOUCH5/ADC1_CH4), UP1.4 (A)
GND: C1.2, C2.2, C3.2, C4.2, C5.2, C6.2, ESP_ENABLE1.1, ESP_PROGRAM1.1, J1.5 (GND), J1.6 (Shield), J2.20, RV1.1, U1.1 (GND), U1.40 (GND), U1.41 (GND), U2.1 (VSS), U2.16 (K), U3.4 (GND)
unnamed: C4.1, D1.1 (K), F1.2, U3.1 (Vcc)
unnamed: F1.1, J1.1 (VBUS)
unnamed: RV1.2, U2.3 (VO)

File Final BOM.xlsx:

Custom Reference YOUR NAME (must have) + refdes (optional)! | TOTAL Qty (for 2 boards, or less if budget constrained) | Manufacturer Part # | Digi-key Part#/SKU | Mouser Part#/SKU | Amazon link LAST RESORT | Price/unit ($) | Reference Designator | Description (include component value if applicable)
Jaden Baptista & Anthony Rubio | 1.0 | NHD-0420H1Z-FSW-GBW-33V3 | NHD-0420H1Z-FSW-GBW-33V3-ND |  |  | 21.38 | U2 | LCD MOD 80DIG 20X4 TRANSFLCT WHT
Jaden Baptista & Anthony Rubio | 1.0 | PTN10-E20HB20 | 2223-PTN10-E20HB20-ND |  |  | 0.65 | RV1 | TRIMMER POTENTIOMETER, 10MM, HOR
Jaden Baptista & Anthony Rubio | 6.0 | 222ADVBA | CT3084-ND |  |  | 0.23 | SW(1-6) | SWITCH TACTILE SPST-NO 0.05A 12V
Jaden Baptista & Anthony Rubio | 1.0 | RC0805JR-0710KL | 311-10KARCT-ND |  |  | 0.1 | R1 | RES 10K OHM 5% 1/8W 0805
Jaden Baptista & Anthony Rubio | 3.0 | CL21B104KBCNNNC | 1276-1003-1-ND |  |  | 0.1 | C2, C5, C6 | CAP CER 0.1UF 50V X7R 0805
Jaden Baptista & Anthony Rubio | 1.0 | MSP430G2553IN20 | 296-28429-5-ND |  |  | 3.16 | FLOATING | MSP430 CPU16 MSP430G2xx Microcontroller IC 16-Bit 16MHz 16KB (16K x 8) FLASH 20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
Jaden Baptista & Anthony Rubio | 1.0 | 110-83-320-41-001101 | 110-83-320-41-001101-ND |  |  | 2.02 | J2 | CONN IC DIP SOCKET 20POS GOLD
Jaden Baptista & Anthony Rubio | 1.0 | ESP32-S2-SOLO-2-N4 | 1965-ESP32-S2-SOLO-2-N4-ND |  |  | 2.6 | U1 | WiFi 802.11b/g/n Transceiver Module 2.4GHz PCB Trace Surface Mount
Jaden Baptista & Anthony Rubio | 1.0 | CL21B105KAFNNNE | 1276-1066-1-ND |  |  | 0.1 | C1 | 1 µF ±10% 25V Ceramic Capacitor X7R 0805 (2012 Metric)
Jaden Baptista & Anthony Rubio | 1.0 | BA033CC0FP-E2 | BA033CC0FP-E2CT-ND |  |  | 1.41 | U3 | IC REG LINEAR 3.3V 1A TO252-3
Jaden Baptista & Anthony Rubio | 1.0 | SS14HE3_B/H | 112-SS14HE3_B/HCT-ND |  |  | 0.09752 | D1 | Diode 40 V 1A Surface Mount DO-214AC (SMA)
Jaden Baptista & Anthony Rubio | 1.0 | 10118194-0011LF | 10118194-0011LF-ND |  |  | 0.27581 | J1 | USB - micro B USB 2.0 Receptacle Connector 5 Position Surface Mount, Right Angl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
Jaden Baptista & Anthony Rubio | 1.0 | 0ZCG0075FF2C | 507-1763-1-ND |  |  | 0.16 | F1 | PTC RESET FUSE 16V 750MA 1812
Jaden Baptista & Anthony Rubio | 2.0 | CL21A106KOQNNNE | 1276-1096-1-ND |  |  | 0.1 | C3, C4 | 10 µF ±10% 16V Ceramic Capacitor X5R 0805 (2012 Metric)

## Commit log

2023-03-20 create kicad project
2023-04-04 working on things
2023-04-05 switch voltage divider for regulator
2023-04-06 use digikey/espressif libraries
2023-04-06 finalize schematic
2023-04-06 update components & footprints
2023-04-06 complete rough footprints
2023-04-06 route rough traces
2023-04-12 rough draft layout
2023-04-12 software examples
2023-04-12 add test points
2023-04-12 just in case
2023-04-17 finalized pcb
2023-04-17 increase mounting drill size by 0.1mm
2023-04-17 add digikey and espressif libs
2023-04-17 move external libs to project list
2023-04-18 fix espressif submodule problem
2023-04-18 gerber files
2023-04-18 zip files
2023-04-18 fix pour to edge clearance
2023-04-18 complete hardware!
2023-06-26 add jtag implementations
2023-07-22 reorganize repository
2023-07-22 clean software folder
2023-07-23 clean repository
2023-07-24 add disassembler
2023-09-17 get msp430 jtag implementation to working state
2023-10-20 improve gitignores
2023-10-20 improve .gitignore
2023-10-20 make various changes, fix .gitignores
2023-12-30 remove ccs cache
2024-05-27 Implement backchannel UART driver
2024-05-28 create testing framework
2024-05-28 begin writing jtag fsm tests
2024-05-29 refactor libraries & remove backchannel tests to fix build errors
2024-05-30 write and pass test_dr_shift test
2024-05-31 write jtag control functions based on slau320
2024-05-31 begin updating fsm tests
2024-06-01 fix testing framework
2024-06-01 write fsm tests
2024-06-01 write control tests
2024-06-03 add blinky and try to fix bug
2024-06-04 fix setTCLK and clrTCLK bug
2024-06-06 add msp430g2553 controller support & purge build dirs
2024-06-06 begin updating pcb with g2553
2024-06-06 route new pcb
2024-06-08 finish disassembler
2024-06-08 add proper special addressing mode support
2024-06-09 fix jump bug and autoincrement constant bug
2024-06-09 refactor appendOperand
2024-06-10 update schematic to use length 40 lcd
2024-06-11 update schematic to active high reset
2024-06-11 reroute pcb for 40 line lcd screen
2024-06-23 begin work on display driver
2024-06-23 remove gerber files
2024-06-27 fix hardware issues and route small pcb
2024-06-28 gerber pcb and update BOM
2024-07-05 implement rudimentary button irq
2024-07-06 add button debouncing
2024-07-07 add move up capability
2024-07-07 refactor disassembler and main
2024-07-11 fix bug when only dest consumes word in double operand
2024-07-17 add limited support for call jump following
2024-07-18 reduce power consumption using low power modes
2024-08-02 clean up button code
2024-08-02 clean up functions & recalibrate debounce value
